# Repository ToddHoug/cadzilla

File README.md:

# CADzilla

CADzilla is an S-100 bus board built around the Hitachi HD63484 Advanced CRT
Controller (ACRTC) paired with a Brooktree Bt453 video DAC. The board
carries about 2.2 MBytes of video memory in total:
- a 2 MByte frame buffer for 8-bit-per-pixel display modes at resolutions
  up to 1024x768;
- a 256 KByte, 1-bit-per-pixel overlay layer, mapped pixel for pixel onto
  the frame buffer and shown on top of it in the Bt453's overlay color. It
  can be drawn, shown and hidden without disturbing the picture underneath,
  which suits text, cursors, grids and annotations.

Board design project: KiCAD schematics/PCB, GAL16V8 PLD logic, and supporting
software projects that run on it (assembled and tested on an emulator).

For the full board reference, see the
[CADzilla User Reference Manual](docs/cadzilla-manual.pdf).

## Design philosophy

CADzilla exists for one reason: to enjoy the graphics board design process
the way I did it forty years ago. The circuit architecture, schematic
design, and PCB layout were all done by hand, with no AI assistance — the
way boards like this were designed back then.

Every component on the board, aside from the modern SRAM used for the
frame buffer, is a part that would have been available in 1984, when the
Hitachi HD63484 was released and the S-100 bus was still a going concern.
As far as I could find, no one had ever built an HD63484-based S-100
board — so I built one.

AI did play a role, but not in the hardware: it made it possible to build
a CP/M software development environment and toolchain for the board that I
could never have put together on my own.

## Layout

- `schematics/` — KiCAD project (schematic, PCB, libraries, fab outputs)
- `pld/` — GAL16V8 PLD source (`src/`) and assembled fuse maps (`jed/`)
- `software/` — software projects targeting the board, grouped by toolchain
  - `asm/` — Digital Research ASM + LOAD: hello, firstdraw, drawdemo
  - `m80/` — Microsoft M80 + L80: the czgfx graphics library, gfxdemo,
    czbasic, testpat
  - `rmac/` — Digital Research RMAC + LINK: rhello, ddcz (GSX-80 driver)
  - `z88dk/` — z88dk z80asm (host cross-assembler): the cz88gfx graphics
    library, zhello, z88demo, autodemo
  - `zcc/` — z88dk zcc (C): chello, cgfxdemo, cgsxdemo, dxfview
- `docs/` — design notes and reference datasheets
  - `docs/cadzilla-manual.pdf` — user reference manual
  - `docs/images/` — logo and other documentation images
- `tools/` — build/assemble/program scripts
- `tests/` — emulator test programs and expected output

## Getting started with the software

The software runs under CP/M 2.2 on altairsim, an Altair/S-100 simulator
with a CADzilla board. Requirements:
- altairsim, built at `~/altairsim/build/altairsim`, on `PATH`, or named
  by `$ALTAIRSIM`.
  - **To see the graphics, altairsim must be built with SDL3**, with an X11
    or Wayland backend.
  - Without SDL3 it builds headless: everything here still builds and runs,
    but no video window ever opens.
  - `altairsim -n -x 'SHOW VERSION'` says which build you have. Its `video`
    row should read `SDL3 -- windowed (...)`, not
    `none -- headless (null display)`.
  - To fix it, build SDL3 with altairsim's own script and link it in
    statically. The headers are listed in altairsim's
    `docs/building-linux.md`; `libxtst-dev` is required, and without the
    X11/Wayland ones SDL3 gets no window backend:
    ```bash
    sudo apt-get install -y build-essential cmake git ninja-build pkg-config \
      libx11-dev libxext-dev libxrandr-dev libxcursor-dev libxi-dev libxfixes-dev \
      libxss-dev libxtst-dev libwayland-dev libxkbcommon-dev wayland-protocols \
      libdecor-0-dev libasound2-dev libpulse-dev
    cd ~/altairsim
    tools/build-sdl3-static.sh           # SDL3, pinned version, into ~/opt/sdl3-static
    cmake -S . -B build -DCMAKE_PREFIX_PATH=$HOME/opt/sdl3-static
    cmake --build build
    ```
    The configure step should report
    `SDL3 found -- video boards enabled (windowed)`;
- a desktop session, for the window: it can't open over plain ssh;
- bash 4.4 or later, python3 and GNU coreutils;
- z88dk, for the z88dk and zcc projects only:
  `sudo snap install z88dk --edge`. The snap only sees paths under `$HOME`,
  so the clone has to be there too.

After cloning, run:

```bash
tools/setup.sh
```

It checks the requirements, then builds every project. Each project gets
its own altairsim machine and CP/M disks in `work/`, and its program on that
disk. Nothing is installed. Without z88dk, the projects that need it are
skipped. `tools/setup.sh --check` runs only the check.

To run a program, start altairsim from the project's `work/`:

```bash
cd software/asm/hello/work
altairsim cadzilla.toml
A0>HELLO
```

- Ctrl-E stops the machine and gives you the `altairsim>` monitor, `RUN`
  carries on, and `QUIT` leaves.
- Wait a moment at `A0>` before stopping: the BIOS writes its last disk
  track to the image only then.

Each project has its own `build.sh`, which rebuilds it onto its disk, e.g.
`software/m80/gfxdemo/build.sh`.
- `--clean` resets the project's disks from the pristine images first.
- A failed build exits non-zero, shows the error lines, and leaves the full
  CP/M transcript in `build/<NAME>.LOG`.

`tools/altairsim/README.md` has the details, and how an AI assistant drives
the same machines.

## Board specification

### I/O address map

The board decodes a single 8-byte-aligned base I/O address, set by SW1
(see below). All board registers are addressed as offsets from that base
address:

| Offset             | Register                                      | Access     |
|---------------------|------------------------------------------------|------------|
| `Base + 0`          | HD63484 Address/Status Register (RS = 0)        | Read/Write |
| `Base + 1`          | MODE register (board configuration, write only) | Write only |
| `Base + 2`          | HD63484 Control/FIFO Register (RS = 1)          | Read/Write |
| `Base + 3`          | Reserved / not decoded                          | —          |
| `Base + 4`–`Base + 7` | Bt453 video DAC registers                     | Read/Write |

### MODE register (`Base + 1`, write only)

| Bit | Name  | Description |
|-----|-------|-------------|
| 0   | HSPOL | Horizontal sync polarity: 0 = positive sync pulse, 1 = negative sync pulse |
| 1   | VSPOL | Vertical sync polarity: 0 = positive sync pulse, 1 = negative sync pulse |
| 2   | AMODE | Address mode: 0 = single access mode, 1 = interleaved access mode |
| 3   | OLEN  | Overlay enable: 0 = overlay plane blanked (shift register loads zeros), 1 = overlay pixels displayed over the frame buffer |
| 4   | OLSEL | Overlay select: 0 = lower half, 1 = upper half of the overlay memory — selects which 64K-word half of the 128K-word overlay SRAM a drawing-mode CHR screen addresses |
| 5–7 | —     | Reserved |

The overlay (U19, 1 bit per pixel, mapped 1:1 onto frame-buffer pixels) is
drawn by targeting an ACRTC screen with the CHR bit set in its Memory Width
register. A CHR screen only has a 64K-word address space, so OLSEL selects
which 64K-word half of the 128K-word overlay SRAM that screen addresses.
OLSEL is cleared to 0 by reset. A CHR screen must never be displayed —
overlay display is driven by the frame buffer's own display cycles,
independent of OLSEL.

### Configuration DIP switch (SW1)

SW1 is an 8-position DIP switch that sets the board's I/O base address and
host interface options:

| Switch          | Function | On | Off |
|-----------------|----------|----|-----|
| SW1-1 – SW1-5   | I/O base address (address bits 7:3) | — | — |
| SW1-6           | HD63484 host bus width | 8-bit host interface: DACK\* follows RESET\*, so it is low during reset | 16-bit host interface: DACK\* is pulled high |
| SW1-7           | 16-bit address decode enable | Decodes the full 16-bit I/O address (A15–A8 must be 00h) | Decodes only the 8-bit I/O address |
| SW1-8           | Interrupt enable | HD63484 interrupt request connected to the S-100 bus | Interrupt request disconnected from the S-100 bus |

### Frame buffer and feature support

- About 2.2 MBytes of video SRAM in total — no refresh cycles required
- 2 MByte frame buffer (U11–U18): 8 bits per pixel only, Graphics Address
  Increment (GAI) = 8
- 256 KByte 1-bit-per-pixel overlay (U19, 128K x 16):
  - mapped 1:1 onto frame-buffer pixels, and read during the frame buffer's
    own display cycles;
  - shown over the picture in the Bt453's programmable overlay color, and
    turned on or off with MODE register bit OLEN;
  - drawn through an ACRTC screen with CHR set, which is never displayed.
    MODE register bit OLSEL selects which half of the overlay it addresses
- The ACRTC's own hardware cursor, superimposed access mode, light pen,
  zooming, video attributes, external sync, and DMA transfers are **not
  supported**. A cursor can be drawn in the overlay instead
- Interrupts are supported, enabled via SW1-8

See the [board manual](docs/cadzilla-manual.pdf) for full details.

## License

Copyright (C) 2026 Todd Houg.

- **Hardware** (the KiCAD schematics and PCB layout in `schematics/`, the
  GAL logic in `pld/`, and the board manual) is licensed under the
  [CERN Open Hardware Licence Version 2 - Permissive](LICENSES/CERN-OHL-P-2.0.txt)
  (CERN-OHL-P-2.0).
- **Software** (everything in `software/`, `tools/` and `tests/`) is
  licensed under the [GNU General Public License](LICENSES/GPL-3.0.txt),
  version 3 or (at your option) any later version (GPL-3.0-or-later).

The manufacturers' datasheets in `docs/datasheets/`, and the
third-party CP/M tools on the disk images, are not covered by either
license. See [LICENSE](LICENSE) for the full breakdown.

See [CLAUDE.md](CLAUDE.md) for AI-assistance working notes.

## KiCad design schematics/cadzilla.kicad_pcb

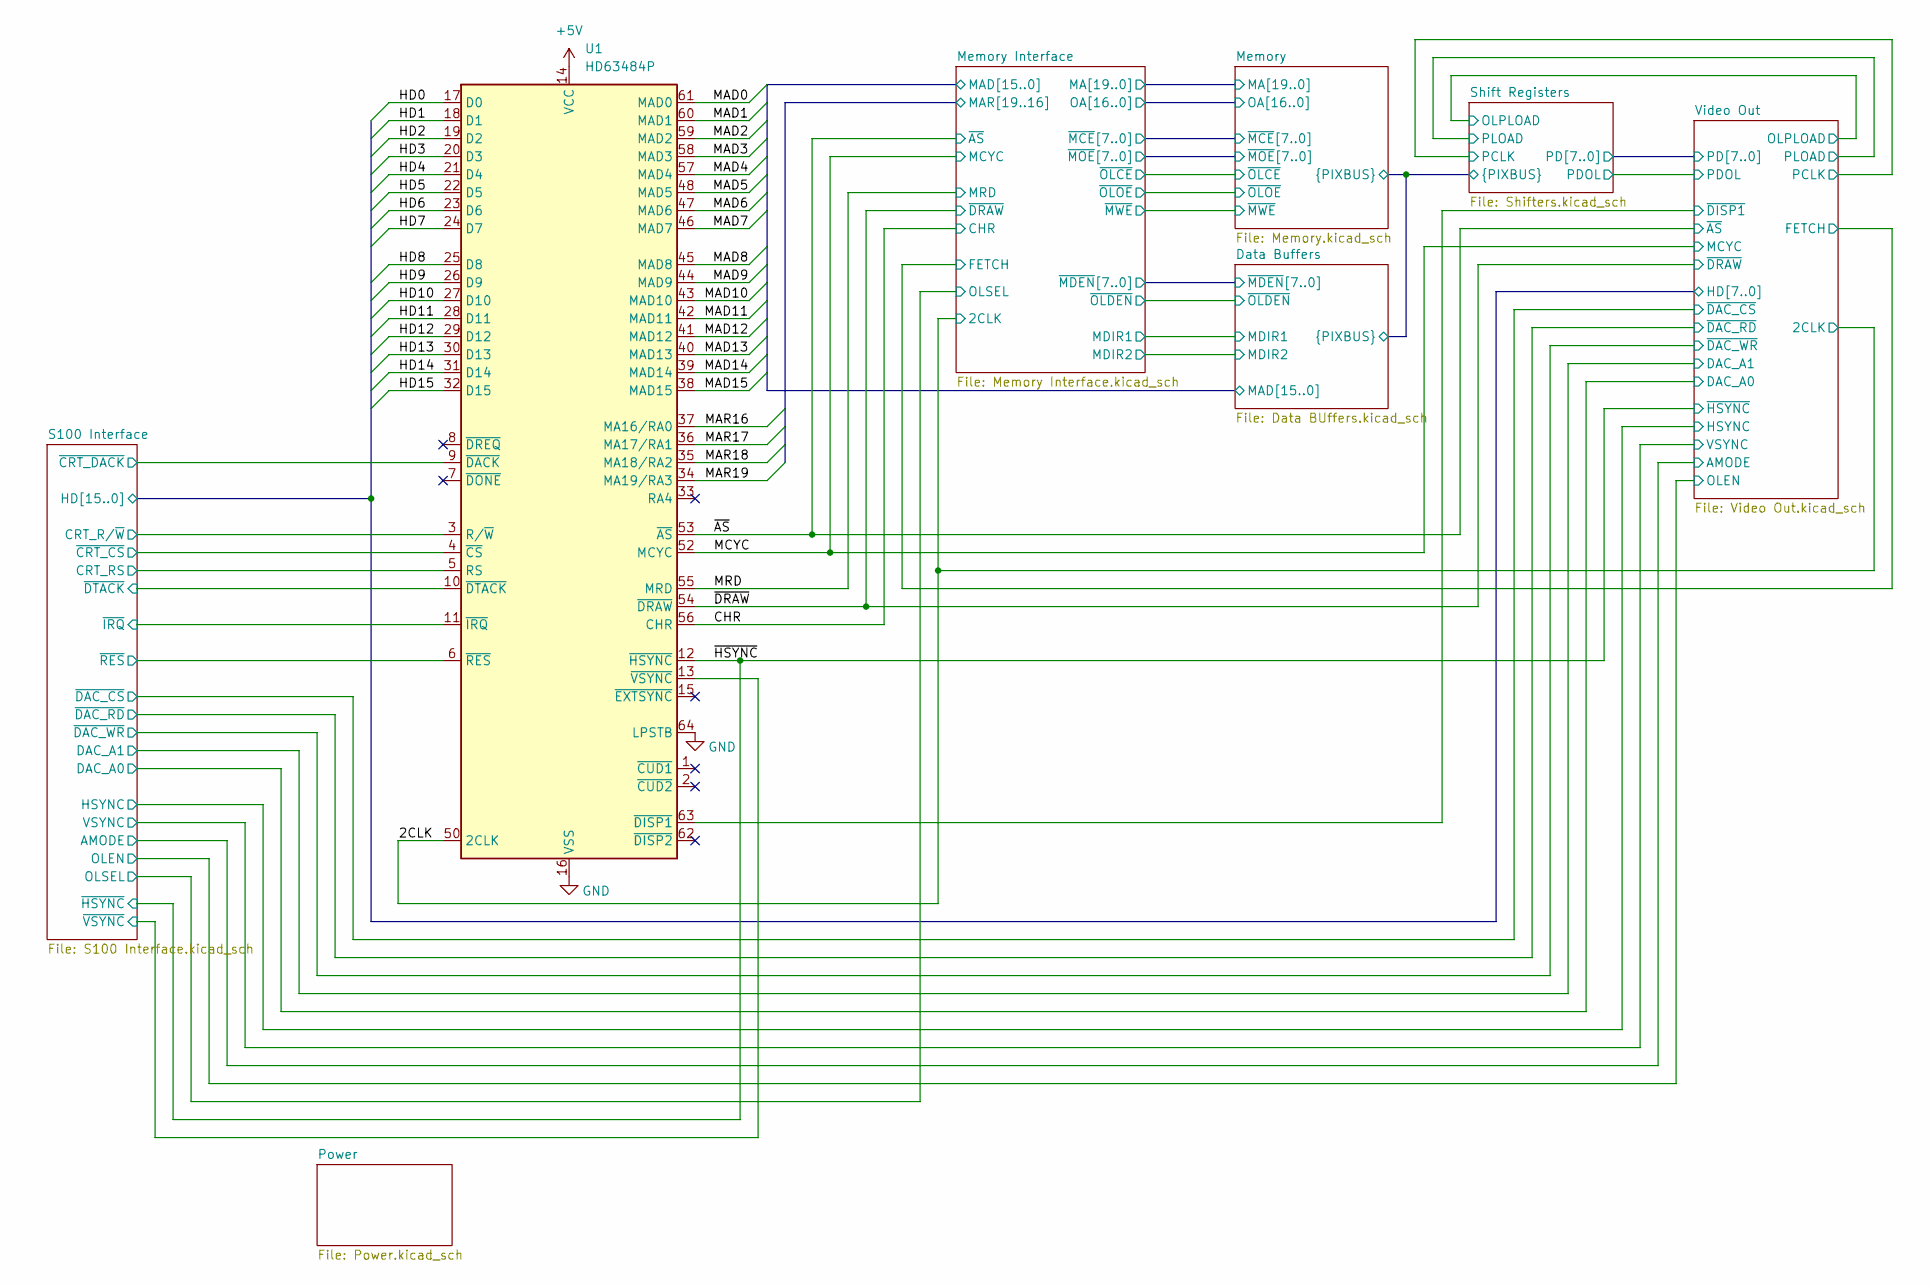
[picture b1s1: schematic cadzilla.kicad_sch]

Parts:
U1: HD63484P; DIP-64_W22.86mm_Socket

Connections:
+5V: U1.14 (VCC), U1.49 (VCC); also elsewhere on the board
/2CLK: U1.50 (2CLK); also elsewhere on the board
/CHR: U1.56 (CHR); also elsewhere on the board
/Data Buffers/MAD0: U1.61 (MAD0); also elsewhere on the board
/Data Buffers/MAD1: U1.60 (MAD1); also elsewhere on the board
/Data Buffers/MAD2: U1.59 (MAD2); also elsewhere on the board
/Data Buffers/MAD3: U1.58 (MAD3); also elsewhere on the board
/Data Buffers/MAD4: U1.57 (MAD4); also elsewhere on the board
/Data Buffers/MAD5: U1.48 (MAD5); also elsewhere on the board
/Data Buffers/MAD6: U1.47 (MAD6); also elsewhere on the board
/Data Buffers/MAD7: U1.46 (MAD7); also elsewhere on the board
/Data Buffers/MAD8: U1.45 (MAD8); also elsewhere on the board
/Data Buffers/MAD9: U1.44 (MAD9); also elsewhere on the board
/Data Buffers/MAD10: U1.43 (MAD10); also elsewhere on the board
/Data Buffers/MAD11: U1.42 (MAD11); also elsewhere on the board
/Data Buffers/MAD12: U1.41 (MAD12); also elsewhere on the board
/Data Buffers/MAD13: U1.40 (MAD13); also elsewhere on the board
/Data Buffers/MAD14: U1.39 (MAD14); also elsewhere on the board
/Data Buffers/MAD15: U1.38 (MAD15); also elsewhere on the board
/MCYC: U1.52 (MCYC); also elsewhere on the board
/MRD: U1.55 (MRD); also elsewhere on the board
/Memory Interface/MAR16: U1.37 (MA16/RA0); also elsewhere on the board
/Memory Interface/MAR17: U1.36 (MA17/RA1); also elsewhere on the board
/Memory Interface/MAR18: U1.35 (MA18/RA2); also elsewhere on the board
/Memory Interface/MAR19: U1.34 (MA19/RA3); also elsewhere on the board
/S100 Interface/CRT_RS: U1.5 (RS); also elsewhere on the board
/S100 Interface/CRT_R/~W: U1.3 (R/~W); also elsewhere on the board
/S100 Interface/HD0: U1.17 (D0); also elsewhere on the board
/S100 Interface/HD1: U1.18 (D1); also elsewhere on the board
/S100 Interface/HD2: U1.19 (D2); also elsewhere on the board
/S100 Interface/HD3: U1.20 (D3); also elsewhere on the board
/S100 Interface/HD4: U1.21 (D4); also elsewhere on the board
/S100 Interface/HD5: U1.22 (D5); also elsewhere on the board
/S100 Interface/HD6: U1.23 (D6); also elsewhere on the board
/S100 Interface/HD7: U1.24 (D7); also elsewhere on the board
/S100 Interface/HD8: U1.25 (D8); also elsewhere on the board
/S100 Interface/HD9: U1.26 (D9); also elsewhere on the board
/S100 Interface/HD10: U1.27 (D10); also elsewhere on the board
/S100 Interface/HD11: U1.28 (D11); also elsewhere on the board
/S100 Interface/HD12: U1.29 (D12); also elsewhere on the board
/S100 Interface/HD13: U1.30 (D13); also elsewhere on the board
/S100 Interface/HD14: U1.31 (D14); also elsewhere on the board
/S100 Interface/HD15: U1.32 (D15); also elsewhere on the board
/S100 Interface/~CRT_CS: U1.4 (~CS); also elsewhere on the board
/S100 Interface/~CRT_DACK: U1.9 (~DACK); also elsewhere on the board
/S100 Interface/~DTACK: U1.10 (~DTACK); also elsewhere on the board
/S100 Interface/~IRQ: U1.11 (~IRQ); also elsewhere on the board
/S100 Interface/~RES: U1.6 (~RES); also elsewhere on the board
/S100 Interface/~VSYNC: U1.13 (~VSYNC); also elsewhere on the board
/Video Out/~DISP1: U1.63 (~DISP1); also elsewhere on the board
/~AS: U1.53 (~AS); also elsewhere on the board
/~DRAW: U1.54 (~DRAW); also elsewhere on the board
/~HSYNC: U1.12 (~HSYNC); also elsewhere on the board
GND: U1.16 (VSS), U1.51 (VSS), U1.64 (LPSTB); also elsewhere on the board

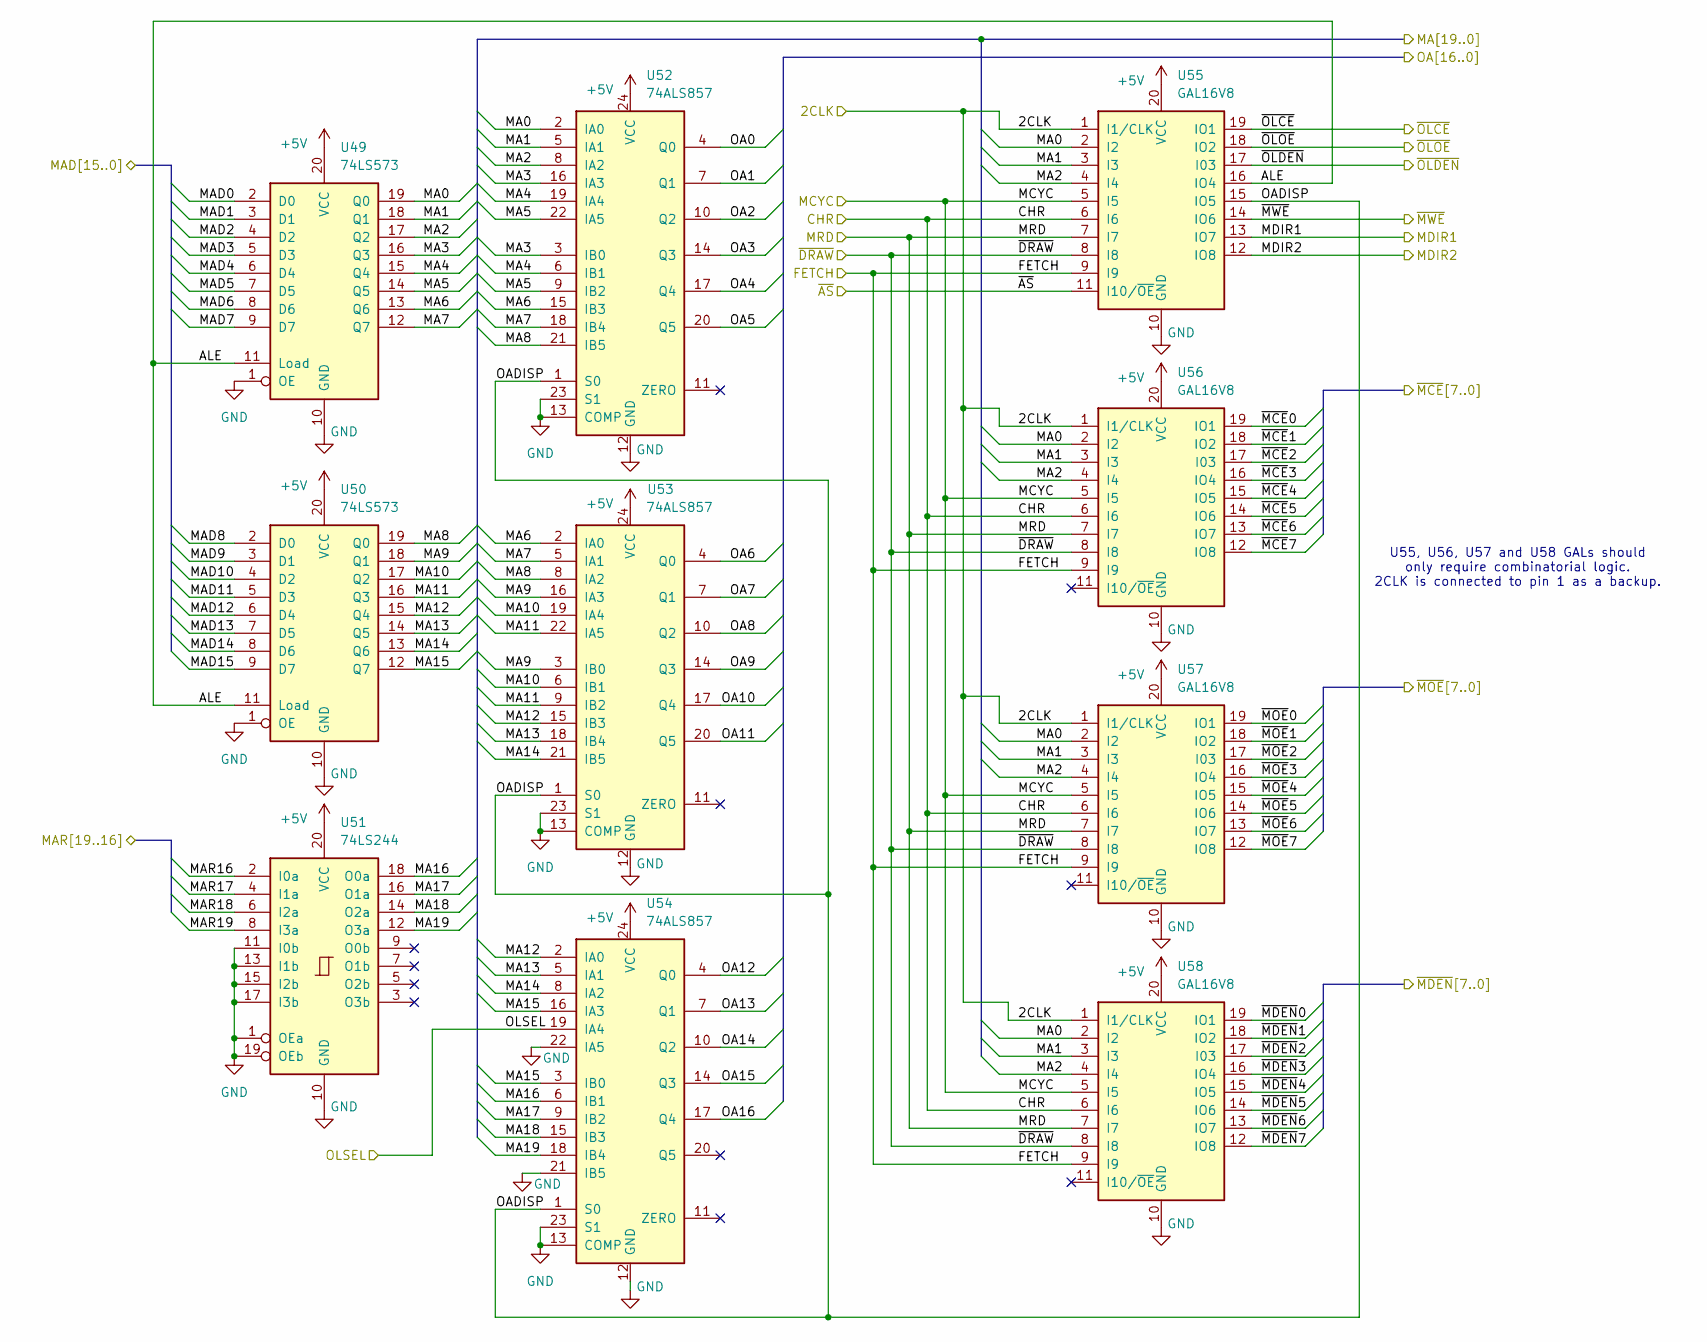
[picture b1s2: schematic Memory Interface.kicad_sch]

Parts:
U49, U50: 74LS573; DIP-20_W7.62mm_Socket
U51: 74LS244; DIP-20_W7.62mm_Socket
U52, U53, U54: 74ALS857; DIP-24_W7.62mm_Socket
U55, U56, U57, U58: GAL16V8; DIP-20_W7.62mm_Socket

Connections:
+5V: U49.20 (VCC), U50.20 (VCC), U51.20 (VCC), U52.24 (VCC), U53.24 (VCC), U54.24 (VCC), U55.20 (VCC), U56.20 (VCC), U57.20 (VCC), U58.20 (VCC); also elsewhere on the board
/2CLK: U55.1 (I1/CLK), U56.1 (I1/CLK), U57.1 (I1/CLK), U58.1 (I1/CLK); also elsewhere on the board
/CHR: U55.6 (I6), U56.6 (I6), U57.6 (I6), U58.6 (I6); also elsewhere on the board
/Data Buffers/MAD0: U49.2 (D0); also elsewhere on the board
/Data Buffers/MAD1: U49.3 (D1); also elsewhere on the board
/Data Buffers/MAD2: U49.4 (D2); also elsewhere on the board
/Data Buffers/MAD3: U49.5 (D3); also elsewhere on the board
/Data Buffers/MAD4: U49.6 (D4); also elsewhere on the board
/Data Buffers/MAD5: U49.7 (D5); also elsewhere on the board
/Data Buffers/MAD6: U49.8 (D6); also elsewhere on the board
/Data Buffers/MAD7: U49.9 (D7); also elsewhere on the board
/Data Buffers/MAD8: U50.2 (D0); also elsewhere on the board
/Data Buffers/MAD9: U50.3 (D1); also elsewhere on the board
/Data Buffers/MAD10: U50.4 (D2); also elsewhere on the board
/Data Buffers/MAD11: U50.5 (D3); also elsewhere on the board
/Data Buffers/MAD12: U50.6 (D4); also elsewhere on the board
/Data Buffers/MAD13: U50.7 (D5); also elsewhere on the board
/Data Buffers/MAD14: U50.8 (D6); also elsewhere on the board
/Data Buffers/MAD15: U50.9 (D7); also elsewhere on the board
/Data Buffers/~MDEN0: U58.19 (IO1); also elsewhere on the board
/Data Buffers/~MDEN1: U58.18 (IO2); also elsewhere on the board
/Data Buffers/~MDEN2: U58.17 (I03); also elsewhere on the board
/Data Buffers/~MDEN3: U58.16 (IO4); also elsewhere on the board
/Data Buffers/~MDEN4: U58.15 (IO5); also elsewhere on the board
/Data Buffers/~MDEN5: U58.14 (IO6); also elsewhere on the board
/Data Buffers/~MDEN6: U58.13 (IO7); also elsewhere on the board
/Data Buffers/~MDEN7: U58.12 (IO8); also elsewhere on the board
/MCYC: U55.5 (I5), U56.5 (I5), U57.5 (I5), U58.5 (I5); also elsewhere on the board
/MRD: U55.7 (I7), U56.7 (I7), U57.7 (I7), U58.7 (I7); also elsewhere on the board
/Memory Interface/ALE: U49.11 (Load), U50.11 (Load), U55.16 (IO4)
/Memory Interface/FETCH: U55.9 (I9), U56.9 (I9), U57.9 (I9), U58.9 (I9); also elsewhere on the board
/Memory Interface/MA0: U49.19 (Q0), U52.2 (IA0), U55.2 (I2), U56.2 (I2), U57.2 (I2), U58.2 (I2)
/Memory Interface/MA1: U49.18 (Q1), U52.5 (IA1), U55.3 (I3), U56.3 (I3), U57.3 (I3), U58.3 (I3)
/Memory Interface/MA2: U49.17 (Q2), U52.8 (IA2), U55.4 (I4), U56.4 (I4), U57.4 (I4), U58.4 (I4)
/Memory Interface/MA3: U49.16 (Q3), U52.3 (IB0), U52.16 (IA3); also elsewhere on the board
/Memory Interface/MA4: U49.15 (Q4), U52.6 (IB1), U52.19 (IA4); also elsewhere on the board
/Memory Interface/MA5: U49.14 (Q5), U52.9 (IB2), U52.22 (IA5); also elsewhere on the board
/Memory Interface/MA6: U49.13 (Q6), U52.15 (IB3), U53.2 (IA0); also elsewhere on the board
/Memory Interface/MA7: U49.12 (Q7), U52.18 (IB4), U53.5 (IA1); also elsewhere on the board
/Memory Interface/MA8: U50.19 (Q0), U52.21 (IB5), U53.8 (IA2); also elsewhere on the board
/Memory Interface/MA9: U50.18 (Q1), U53.3 (IB0), U53.16 (IA3); also elsewhere on the board
/Memory Interface/MA10: U50.17 (Q2), U53.6 (IB1), U53.19 (IA4); also elsewhere on the board
/Memory Interface/MA11: U50.16 (Q3), U53.9 (IB2), U53.22 (IA5); also elsewhere on the board
/Memory Interface/MA12: U50.15 (Q4), U53.15 (IB3), U54.2 (IA0); also elsewhere on the board
/Memory Interface/MA13: U50.14 (Q5), U53.18 (IB4), U54.5 (IA1); also elsewhere on the board
/Memory Interface/MA14: U50.13 (Q6), U53.21 (IB5), U54.8 (IA2); also elsewhere on the board
/Memory Interface/MA15: U50.12 (Q7), U54.3 (IB0), U54.16 (IA3); also elsewhere on the board
/Memory Interface/MA16: U51.18 (O0a), U54.6 (IB1); also elsewhere on the board
/Memory Interface/MA17: U51.16 (O1a), U54.9 (IB2); also elsewhere on the board
/Memory Interface/MA18: U51.14 (O2a), U54.15 (IB3); also elsewhere on the board
/Memory Interface/MA19: U51.12 (O3a), U54.18 (IB4); also elsewhere on the board
/Memory Interface/MAR16: U51.2 (I0a); also elsewhere on the board
/Memory Interface/MAR17: U51.4 (I1a); also elsewhere on the board
/Memory Interface/MAR18: U51.6 (I2a); also elsewhere on the board
/Memory Interface/MAR19: U51.8 (I3a); also elsewhere on the board
/Memory Interface/MDIR1: U55.13 (IO7); also elsewhere on the board
/Memory Interface/MDIR2: U55.12 (IO8); also elsewhere on the board
/Memory Interface/OA0: U52.4 (Q0); also elsewhere on the board
/Memory Interface/OA1: U52.7 (Q1); also elsewhere on the board
/Memory Interface/OA2: U52.10 (Q2); also elsewhere on the board
/Memory Interface/OA3: U52.14 (Q3); also elsewhere on the board
/Memory Interface/OA4: U52.17 (Q4); also elsewhere on the board
/Memory Interface/OA5: U52.20 (Q5); also elsewhere on the board
/Memory Interface/OA6: U53.4 (Q0); also elsewhere on the board
/Memory Interface/OA7: U53.7 (Q1); also elsewhere on the board
/Memory Interface/OA8: U53.10 (Q2); also elsewhere on the board
/Memory Interface/OA9: U53.14 (Q3); also elsewhere on the board
/Memory Interface/OA10: U53.17 (Q4); also elsewhere on the board
/Memory Interface/OA11: U53.20 (Q5); also elsewhere on the board
/Memory Interface/OA12: U54.4 (Q0); also elsewhere on the board
/Memory Interface/OA13: U54.7 (Q1); also elsewhere on the board
/Memory Interface/OA14: U54.10 (Q2); also elsewhere on the board
/Memory Interface/OA15: U54.14 (Q3); also elsewhere on the board
/Memory Interface/OA16: U54.17 (Q4); also elsewhere on the board
/Memory Interface/OADISP: U52.1 (S0), U53.1 (S0), U54.1 (S0), U55.15 (IO5)
/Memory Interface/OLSEL: U54.19 (IA4); also elsewhere on the board
/Memory Interface/~MCE0: U56.19 (IO1); also elsewhere on the board
/Memory Interface/~MCE1: U56.18 (IO2); also elsewhere on the board
/Memory Interface/~MCE2: U56.17 (I03); also elsewhere on the board
/Memory Interface/~MCE3: U56.16 (IO4); also elsewhere on the board
/Memory Interface/~MCE4: U56.15 (IO5); also elsewhere on the board
/Memory Interface/~MCE5: U56.14 (IO6); also elsewhere on the board
/Memory Interface/~MCE6: U56.13 (IO7); also elsewhere on the board
/Memory Interface/~MCE7: U56.12 (IO8); also elsewhere on the board
/Memory Interface/~MOE0: U57.19 (IO1); also elsewhere on the board
/Memory Interface/~MOE1: U57.18 (IO2); also elsewhere on the board
/Memory Interface/~MOE2: U57.17 (I03); also elsewhere on the board
/Memory Interface/~MOE3: U57.16 (IO4); also elsewhere on the board
/Memory Interface/~MOE4: U57.15 (IO5); also elsewhere on the board
/Memory Interface/~MOE5: U57.14 (IO6); also elsewhere on the board
/Memory Interface/~MOE6: U57.13 (IO7); also elsewhere on the board
/Memory Interface/~MOE7: U57.12 (IO8); also elsewhere on the board
/Memory Interface/~MWE: U55.14 (IO6); also elsewhere on the board
/Memory Interface/~OLCE: U55.19 (IO1); also elsewhere on the board
/Memory Interface/~OLDEN: U55.17 (I03); also elsewhere on the board
/Memory Interface/~OLOE: U55.18 (IO2); also elsewhere on the board
/~AS: U55.11 (I10/~OE); also elsewhere on the board
/~DRAW: U55.8 (I8), U56.8 (I8), U57.8 (I8), U58.8 (I8); also elsewhere on the board
GND: U49.1 (OE), U49.10 (GND), U50.1 (OE), U50.10 (GND), U51.1 (OEa), U51.10 (GND), U51.11 (I0b), U51.13 (I1b), U51.15 (I2b), U51.17 (I3b), U51.19 (OEb), U52.12 (GND), U52.13 (COMP), U52.23 (S1), U53.12 (GND), U53.13 (COMP), U53.23 (S1), U54.12 (GND), U54.13 (COMP), U54.21 (IB5), U54.22 (IA5), U54.23 (S1), U55.10 (GND), U56.10 (GND), U57.10 (GND), U58.10 (GND); also elsewhere on the board

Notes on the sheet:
U55, U56, U57 and U58 GALs should only require combinatorial logic. 2CLK is connected to pin 1 as a backup.

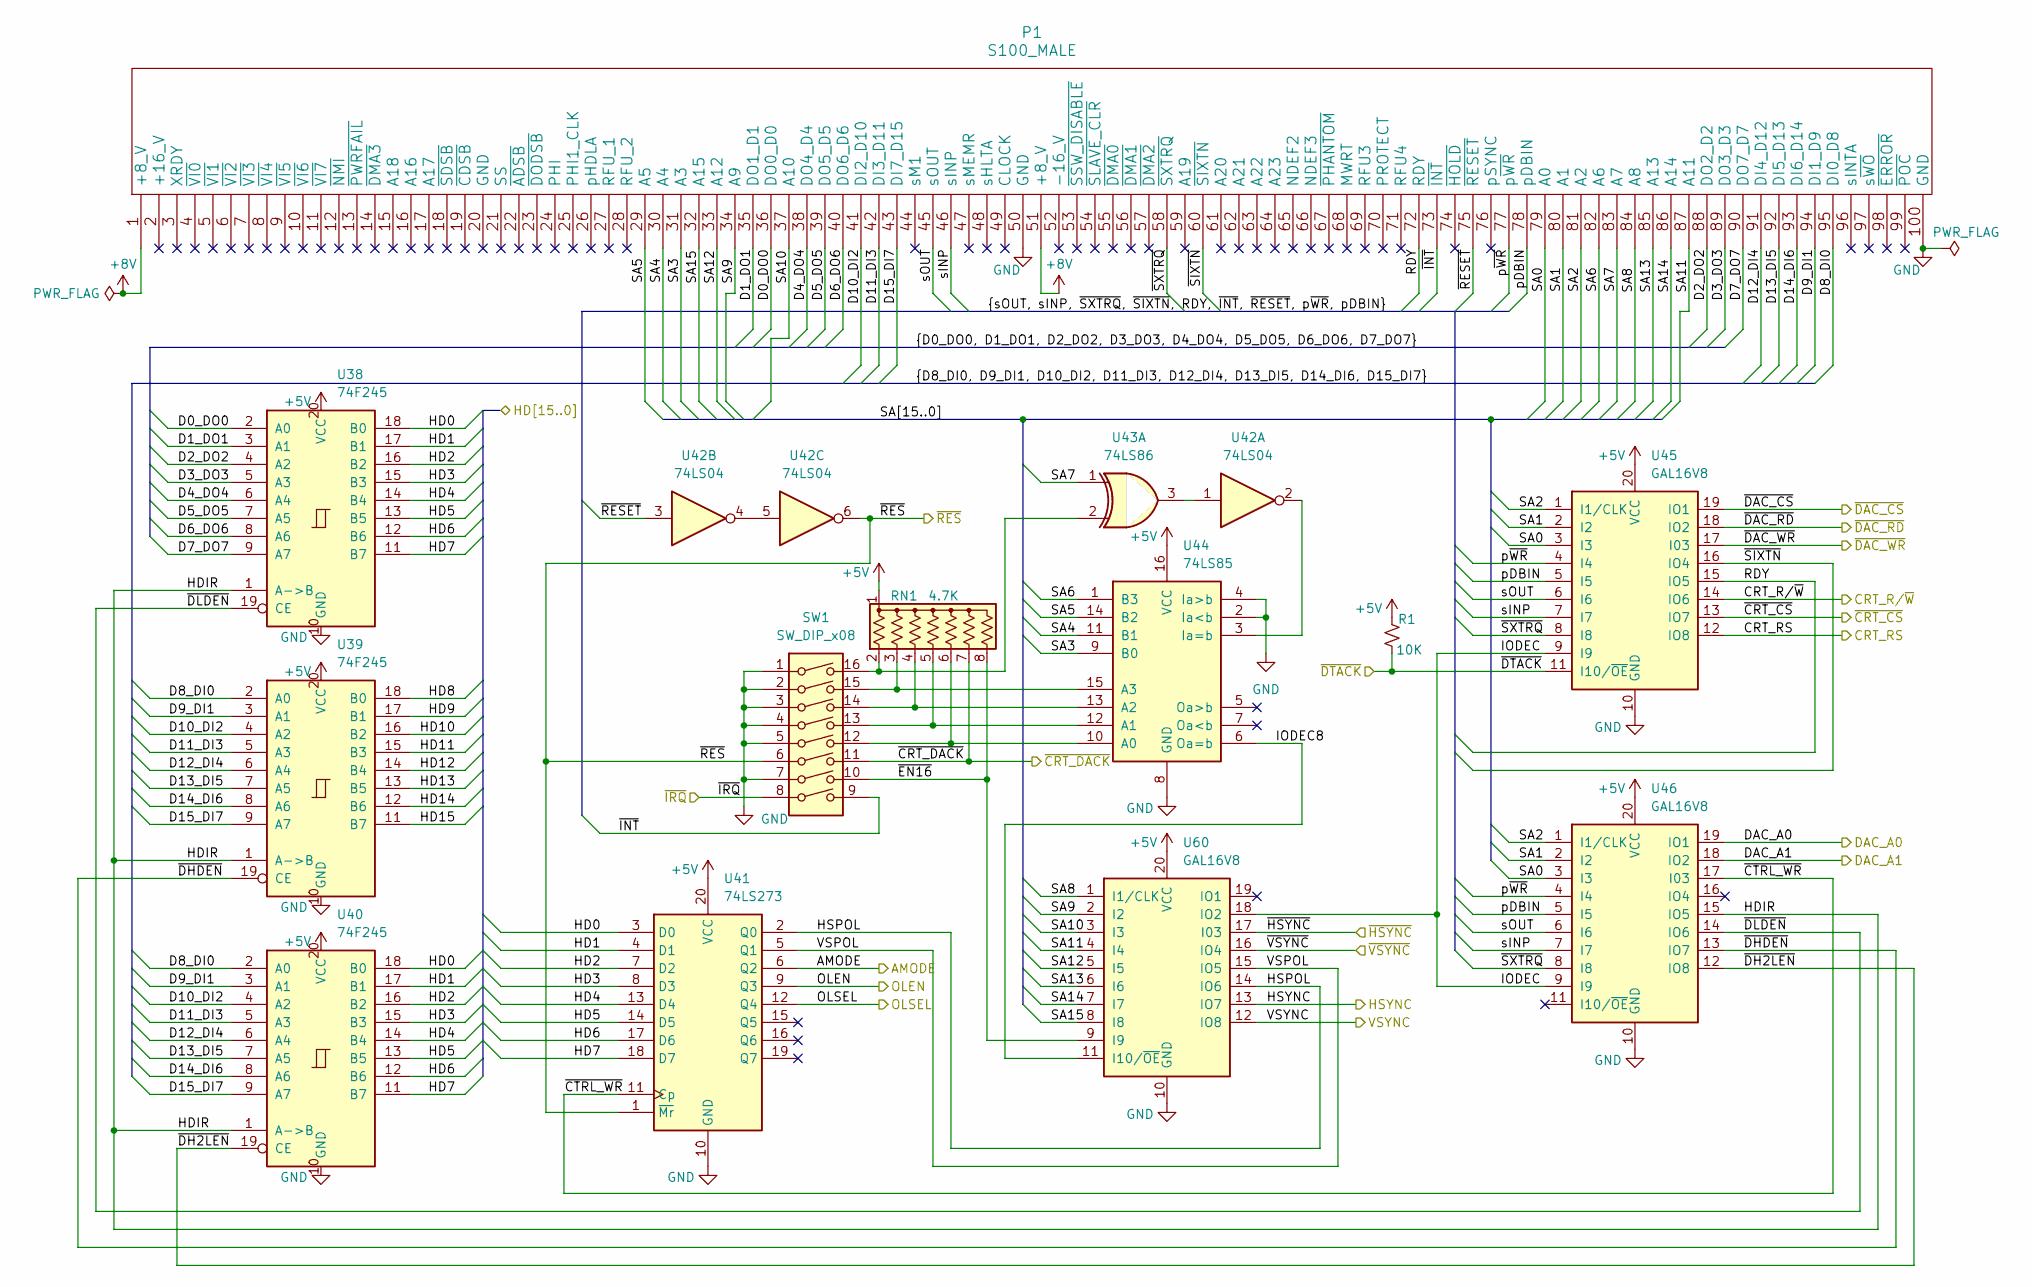
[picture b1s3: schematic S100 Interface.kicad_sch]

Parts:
P1: S100_MALE
R1: 10K; R_Axial_DIN0204_L3.6mm_D1.6mm_P7.62mm_Horizontal
RN1: 4.7K; R_Array_SIP8
SW1: SW_DIP_x08; DIP-16_W7.62mm_Socket
U38, U39, U40: 74F245; DIP-20_W7.62mm_Socket
U41: 74LS273; DIP-20_W7.62mm_Socket
U42: 74LS04; DIP-14_W7.62mm_Socket
U43: 74LS86; DIP-14_W7.62mm_Socket
U44: 74LS85; DIP-16_W7.62mm_Socket
U45, U46: GAL16V8; DIP-20_W7.62mm_Socket
U60: GAL16V8; DIP-20_W7.62mm_Socket_Small_Pads

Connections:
+5V: R1.1, RN1.1 (common), U38.20 (VCC), U39.20 (VCC), U40.20 (VCC), U41.20 (VCC), U44.16 (VCC), U45.20 (VCC), U46.20 (VCC), U60.20 (VCC); also elsewhere on the board
+8V: P1.1 (+8_V), P1.51 (+8_V); also elsewhere on the board
/Memory Interface/OLSEL: U41.12 (Q4); also elsewhere on the board
/S100 Interface/AMODE: U41.6 (Q2); also elsewhere on the board
/S100 Interface/CRT_RS: U45.12 (IO8); also elsewhere on the board
/S100 Interface/CRT_R/~W: U45.14 (IO6); also elsewhere on the board
/S100 Interface/D0_DO0: P1.36 (DO0_D0), U38.2 (A0)
/S100 Interface/D1_DO1: P1.35 (DO1_D1), U38.3 (A1)
/S100 Interface/D2_DO2: P1.88 (DO2_D2), U38.4 (A2)
/S100 Interface/D3_DO3: P1.89 (DO3_D3), U38.5 (A3)
/S100 Interface/D4_DO4: P1.38 (DO4_D4), U38.6 (A4)
/S100 Interface/D5_DO5: P1.39 (DO5_D5), U38.7 (A5)
/S100 Interface/D6_DO6: P1.40 (DO6_D6), U38.8 (A6)
/S100 Interface/D7_DO7: P1.90 (DO7_D7), U38.9 (A7)
/S100 Interface/D8_DI0: P1.95 (DI0_D8), U39.2 (A0), U40.2 (A0)
/S100 Interface/D9_DI1: P1.94 (DI1_D9), U39.3 (A1), U40.3 (A1)
/S100 Interface/D10_DI2: P1.41 (DI2_D10), U39.4 (A2), U40.4 (A2)
/S100 Interface/D11_DI3: P1.42 (DI3_D11), U39.5 (A3), U40.5 (A3)
/S100 Interface/D12_DI4: P1.91 (DI4_D12), U39.6 (A4), U40.6 (A4)
/S100 Interface/D13_DI5: P1.92 (DI5_D13), U39.7 (A5), U40.7 (A5)
/S100 Interface/D14_DI6: P1.93 (DI6_D14), U39.8 (A6), U40.8 (A6)
/S100 Interface/D15_DI7: P1.43 (DI7_D15), U39.9 (A7), U40.9 (A7)
/S100 Interface/DAC_A0: U46.19 (IO1); also elsewhere on the board
/S100 Interface/DAC_A1: U46.18 (IO2); also elsewhere on the board
/S100 Interface/HD0: U38.18 (B0), U40.18 (B0), U41.3 (D0); also elsewhere on the board
/S100 Interface/HD1: U38.17 (B1), U40.17 (B1), U41.4 (D1); also elsewhere on the board
/S100 Interface/HD2: U38.16 (B2), U40.16 (B2), U41.7 (D2); also elsewhere on the board
/S100 Interface/HD3: U38.15 (B3), U40.15 (B3), U41.8 (D3); also elsewhere on the board
/S100 Interface/HD4: U38.14 (B4), U40.14 (B4), U41.13 (D4); also elsewhere on the board
/S100 Interface/HD5: U38.13 (B5), U40.13 (B5), U41.14 (D5); also elsewhere on the board
/S100 Interface/HD6: U38.12 (B6), U40.12 (B6), U41.17 (D6); also elsewhere on the board
/S100 Interface/HD7: U38.11 (B7), U40.11 (B7), U41.18 (D7); also elsewhere on the board
/S100 Interface/HD8: U39.18 (B0); also elsewhere on the board
/S100 Interface/HD9: U39.17 (B1); also elsewhere on the board
/S100 Interface/HD10: U39.16 (B2); also elsewhere on the board
/S100 Interface/HD11: U39.15 (B3); also elsewhere on the board
/S100 Interface/HD12: U39.14 (B4); also elsewhere on the board
/S100 Interface/HD13: U39.13 (B5); also elsewhere on the board
/S100 Interface/HD14: U39.12 (B6); also elsewhere on the board
/S100 Interface/HD15: U39.11 (B7); also elsewhere on the board
/S100 Interface/HDIR: U38.1 (A->B), U39.1 (A->B), U40.1 (A->B), U46.15 (IO5)
/S100 Interface/HSPOL: U41.2 (Q0), U60.14 (IO6)
/S100 Interface/HSYNC: U60.13 (IO7); also elsewhere on the board
/S100 Interface/IODEC: U45.9 (I9), U46.9 (I9), U60.18 (IO2)
/S100 Interface/IODEC8: U44.6 (Oa=b), U60.11 (I10/~OE)
/S100 Interface/OLEN: U41.9 (Q3); also elsewhere on the board
/S100 Interface/RDY: P1.72 (RDY), U45.15 (IO5)
/S100 Interface/SA0: P1.79 (A0), U45.3 (I3), U46.3 (I3)
/S100 Interface/SA1: P1.80 (A1), U45.2 (I2), U46.2 (I2)
/S100 Interface/SA2: P1.81 (A2), U45.1 (I1/CLK), U46.1 (I1/CLK)
/S100 Interface/SA3: P1.31 (A3), U44.9 (B0)
/S100 Interface/SA4: P1.30 (A4), U44.11 (B1)
/S100 Interface/SA5: P1.29 (A5), U44.14 (B2)
/S100 Interface/SA6: P1.82 (A6), U44.1 (B3)
/S100 Interface/SA7: P1.83 (A7), U43.1
/S100 Interface/SA8: P1.84 (A8), U60.1 (I1/CLK)
/S100 Interface/SA9: P1.34 (A9), U60.2 (I2)
/S100 Interface/SA10: P1.37 (A10), U60.3 (I3)
/S100 Interface/SA11: P1.87 (A11), U60.4 (I4)
/S100 Interface/SA12: P1.33 (A12), U60.5 (I5)
/S100 Interface/SA13: P1.85 (A13), U60.6 (I6)
/S100 Interface/SA14: P1.86 (A14), U60.7 (I7)
/S100 Interface/SA15: P1.32 (A15), U60.8 (I8)
/S100 Interface/VSPOL: U41.5 (Q1), U60.15 (IO5)
/S100 Interface/VSYNC: U60.12 (IO8); also elsewhere on the board
/S100 Interface/pDBIN: P1.78 (pDBIN), U45.5 (I5), U46.5 (I5)
/S100 Interface/p~WR: P1.77 (p~WR), U45.4 (I4), U46.4 (I4)
/S100 Interface/sINP: P1.46 (sINP), U45.7 (I7), U46.7 (I7)
/S100 Interface/sOUT: P1.45 (sOUT), U45.6 (I6), U46.6 (I6)
/S100 Interface/~CRT_CS: U45.13 (IO7); also elsewhere on the board
/S100 Interface/~CRT_DACK: RN1.7 (R6), SW1.11; also elsewhere on the board
/S100 Interface/~CTRL_WR: U41.11 (Cp), U46.17 (I03)
/S100 Interface/~DAC_CS: U45.19 (IO1); also elsewhere on the board
/S100 Interface/~DAC_RD: U45.18 (IO2); also elsewhere on the board
/S100 Interface/~DAC_WR: U45.17 (I03); also elsewhere on the board
/S100 Interface/~DH2LEN: U40.19 (CE), U46.12 (IO8)
/S100 Interface/~DHDEN: U39.19 (CE), U46.13 (IO7)
/S100 Interface/~DLDEN: U38.19 (CE), U46.14 (IO6)
/S100 Interface/~DTACK: R1.2, U45.11 (I10/~OE); also elsewhere on the board
/S100 Interface/~EN16: RN1.8 (R7), SW1.10, U60.9 (I9)
/S100 Interface/~INT: P1.73 (~INT), SW1.9
/S100 Interface/~IRQ: SW1.8; also elsewhere on the board
/S100 Interface/~RESET: P1.75 (~RESET), U42.3
/S100 Interface/~RES: SW1.6, U41.1 (~Mr), U42.6; also elsewhere on the board
/S100 Interface/~SIXTN: P1.60 (~SIXTN), U45.16 (IO4)
/S100 Interface/~SXTRQ: P1.58 (~SXTRQ), U45.8 (I8), U46.8 (I8)
/S100 Interface/~VSYNC: U60.16 (IO4); also elsewhere on the board
/~HSYNC: U60.17 (I03); also elsewhere on the board
GND: P1.50 (GND), P1.100 (GND), SW1.1, SW1.2, SW1.3, SW1.4, SW1.5, SW1.7, U38.10 (GND), U39.10 (GND), U40.10 (GND), U41.10 (GND), U44.2 (Ia<b), U44.4 (Ia>b), U44.8 (GND), U45.10 (GND), U46.10 (GND), U60.10 (GND); also elsewhere on the board
unnamed: RN1.2 (R1), SW1.16, U43.2
unnamed: RN1.3 (R2), SW1.15, U44.15 (A3)
unnamed: RN1.4 (R3), SW1.14, U44.13 (A2)
unnamed: RN1.5 (R4), SW1.13, U44.12 (A1)
unnamed: RN1.6 (R5), SW1.12, U44.10 (A0)
unnamed: U42.1, U43.3
unnamed: U42.4, U42.5
unnamed: U42.2, U44.3 (Ia=b)

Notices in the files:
schematics/cadzilla.kicad_pcb:
Copyright 2026 Todd Houg
Licensed under CERN-OHL-P v2
